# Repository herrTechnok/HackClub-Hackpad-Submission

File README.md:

# HackClub-Hackpad-Submission

Schematic            |  PCB         |   Case
----------------------:|:-------------------------:|:-------------------------:|
    |    | 

### What is it for?
I want to be able to easily control the lights on my desk using Shortcuts and Home Assistant. 

### Hurdles
It took me an hour to import the symbol and footprint libraries. 😅

### BOM
- 4x Cherry MX Blue
- 2x SK6812 MINI Leds
- 1x XIAO RP2040
- 4x Beige DSA Keycaps
- 4x M3x16 Bolt
- 4x M3 Heatset

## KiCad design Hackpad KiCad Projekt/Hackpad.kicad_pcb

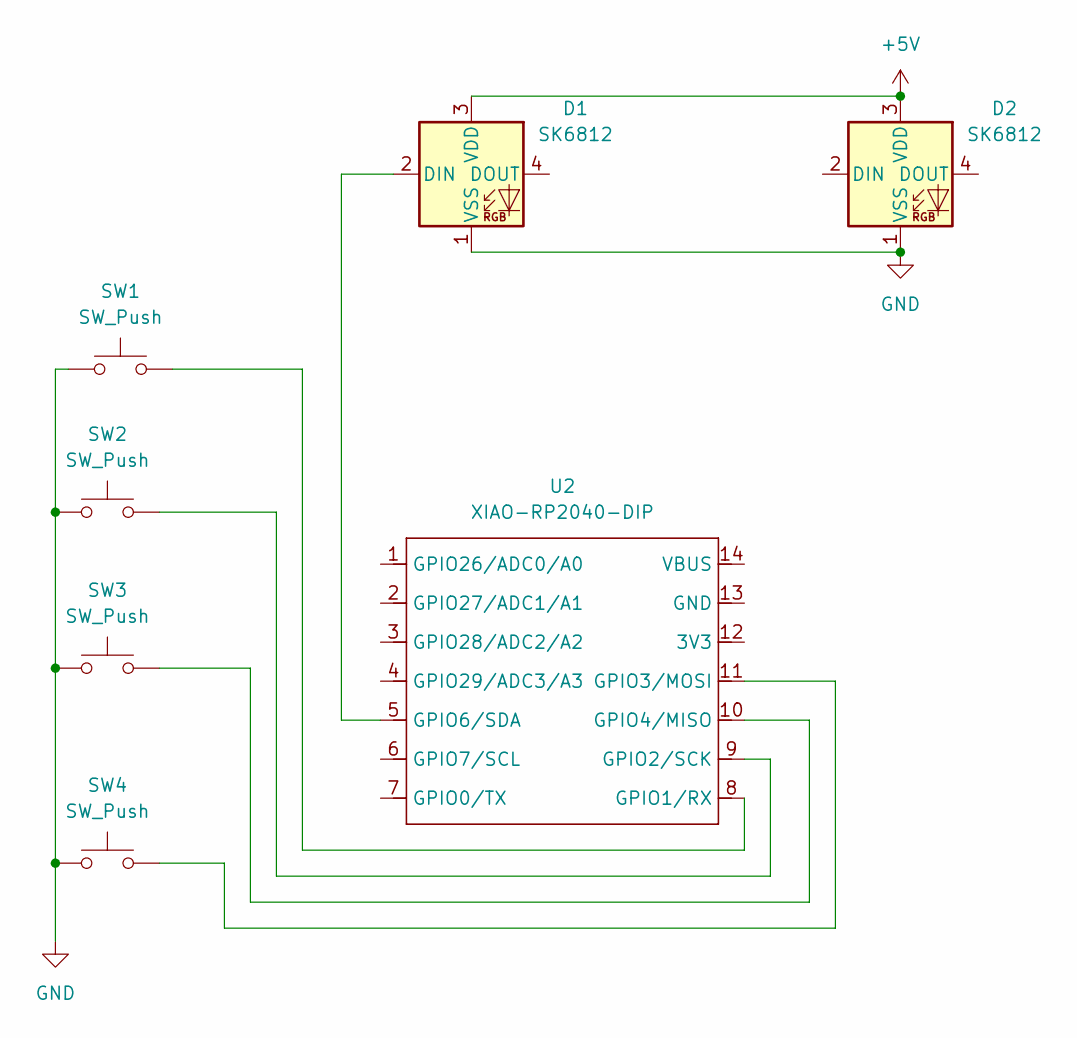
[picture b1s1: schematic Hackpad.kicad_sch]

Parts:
D1, D2: SK6812; LED_SK6812_PLCC4_5.0x5.0mm_P3.2mm
SW1, SW2, SW3, SW4: SW_Push; SW_Cherry_MX_1.00u_PCB
U2: XIAO-RP2040-DIP

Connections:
+5V: D1.3 (VDD), D2.3 (VDD)
GND: D1.1 (VSS), D2.1 (VSS), SW1.1, SW2.1, SW3.1, SW4.1
unnamed: D1.2 (DIN), U2.5 (GPIO6/SDA)
unnamed: SW1.2, U2.8 (GPIO1/RX)
unnamed: SW2.2, U2.9 (GPIO2/SCK)
unnamed: SW4.2, U2.11 (GPIO3/MOSI)
unnamed: SW3.2, U2.10 (GPIO4/MISO)

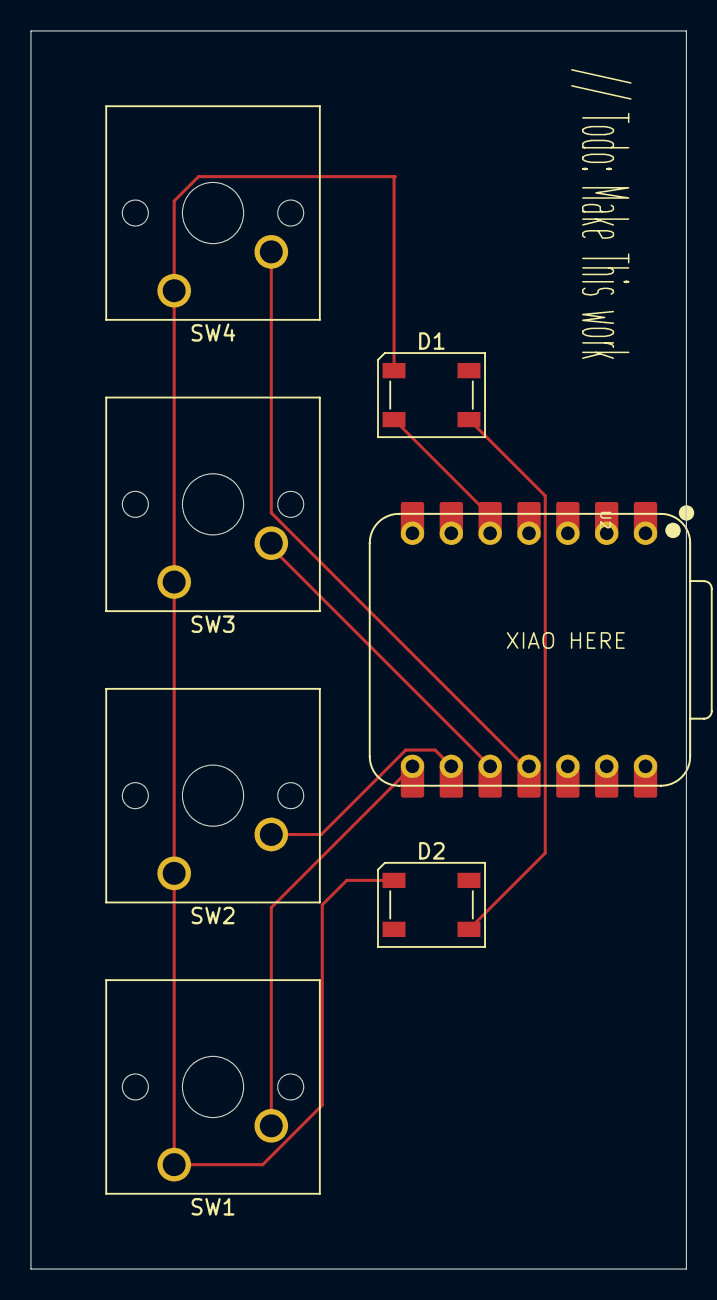
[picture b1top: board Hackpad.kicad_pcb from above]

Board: 2 copper layers, 42.9 x 81.0 mm, 7 parts (0 on the bottom side), 7 nets.

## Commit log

2025-05-30 Upload
2025-06-05 Organised files and wrote the code
2025-06-05 Add Pictured
2025-06-05 Final Toutches
